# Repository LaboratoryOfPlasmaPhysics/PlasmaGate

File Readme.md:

# PlasmaGate: Open-Source FPGA Development Board for laboratory instrumentation

PlasmaGate is an open-source FPGA development board designed for laboratory instrumentation. It is based on the Lattice LFE5U-85F FPGA and designed to be used together with custom daughter boards. The board is equipped with a variety of interfaces including USB 2.0 HS, microSD, on board JTAG (rp2040), 44 GPIO pins, 32MB of SDRAM.

## Features
- Lattice LFE5U-85F FPGA
- USB 2.0 HS interface
- microSD card slot
- On-board JTAG interface using RP2040
- 44 GPIO pins
- 32MB SDRAM
- Customizable daughter board interface
- Open-source design

## Online view
You can view the board design online using kicanvas:
[PlasmaGate Board Design](https://kicanvas.org/?github=https%3A%2F%2Fgithub.com%2FLaboratoryOfPlasmaPhysics%2FPlasmaGate)

## Getting Started
TBD

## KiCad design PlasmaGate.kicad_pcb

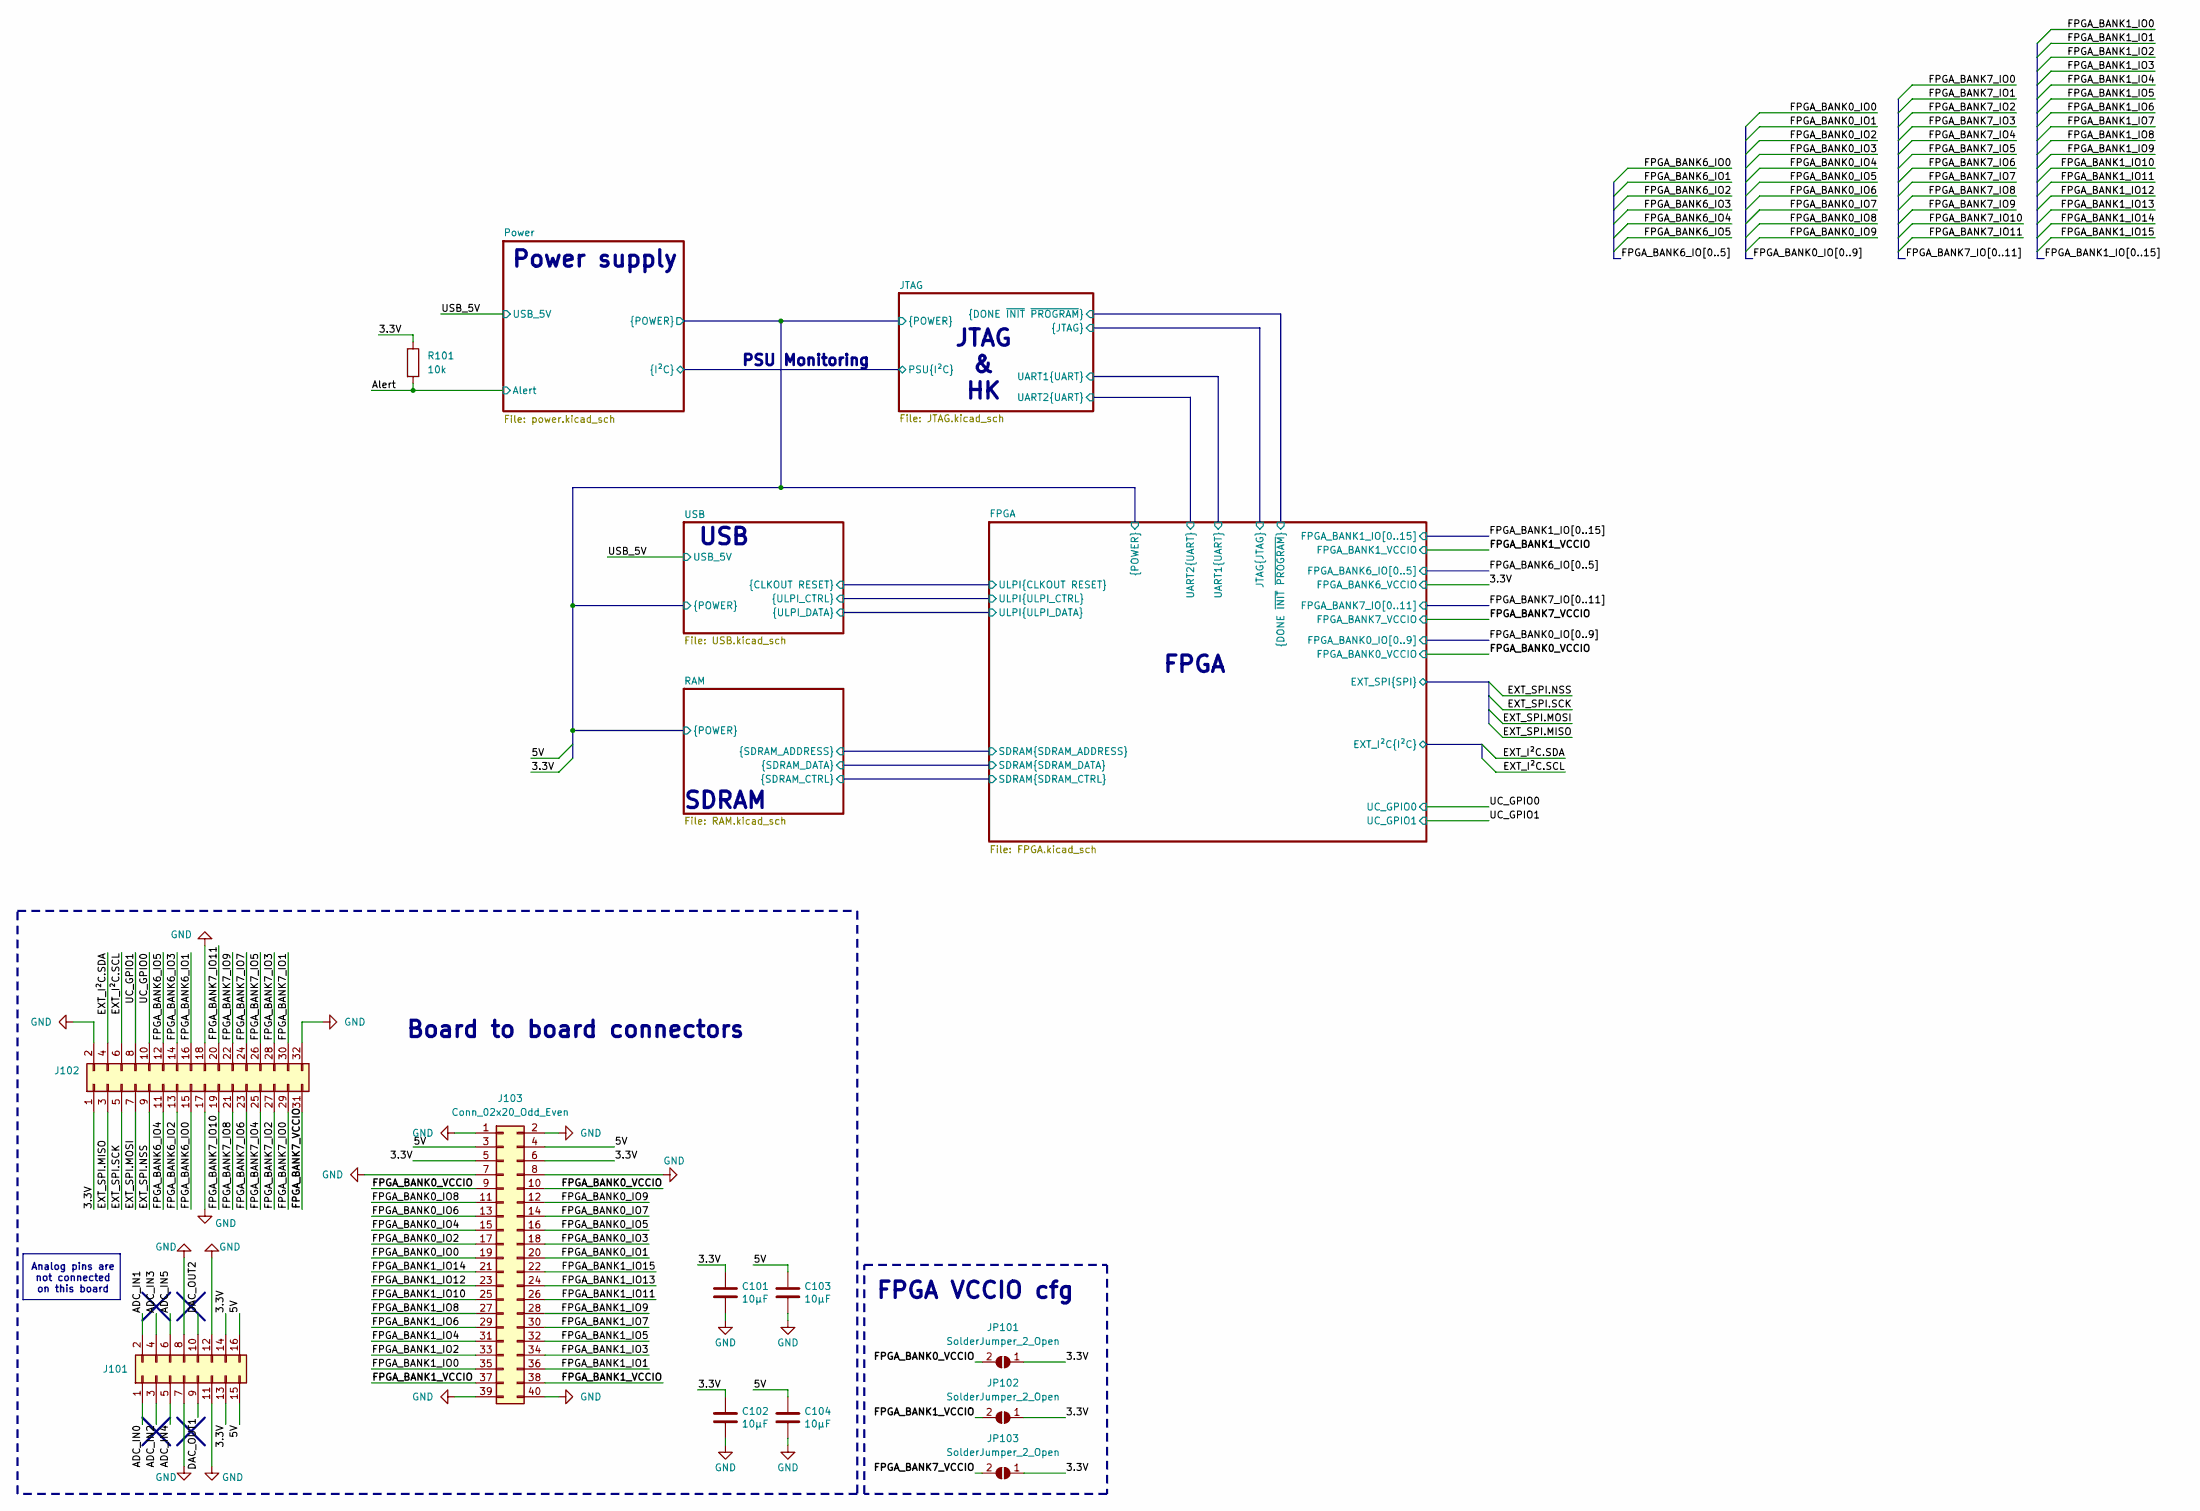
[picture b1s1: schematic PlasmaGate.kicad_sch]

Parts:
C101, C102, C103, C104: 10µF; C_1206_3216Metric_Pad1.33x1.80mm_HandSolder
J101: Conn_02x08_Odd_Even; PinSocket_2x08_P2.54mm_Vertical
J102: Conn_02x16_Odd_Even; PinSocket_2x16_P2.54mm_Vertical
J103: Conn_02x20_Odd_Even; PinSocket_2x20_P2.54mm_Vertical
JP101, JP102, JP103: SolderJumper_2_Open; SolderJumper-2_P1.3mm_Open_TrianglePad1.0x1.5mm
R101: 10k; R_0402_1005Metric_Pad0.72x0.64mm_HandSolder

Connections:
/ADC_IN0: J101.1
/ADC_IN1: J101.2
/ADC_IN2: J101.3
/ADC_IN3: J101.4
/ADC_IN4: J101.5
/ADC_IN5: J101.6
/Alert: R101.2; also elsewhere on the board
/DAC_OUT1: J101.9
/DAC_OUT2: J101.10
/FPGA/3.3V: C101.1, C102.1, J101.13, J101.14, J102.1, J103.5, J103.6, JP101.1 (A), JP102.1 (A), JP103.1 (A), R101.1; also elsewhere on the board
/FPGA/5V: C103.1, C104.1, J101.15, J101.16, J103.3, J103.4; also elsewhere on the board
/FPGA/EXT_I²C.SCL: J102.6; also elsewhere on the board
/FPGA/EXT_I²C.SDA: J102.4; also elsewhere on the board
/FPGA/EXT_SPI.MISO: J102.3; also elsewhere on the board
/FPGA/EXT_SPI.MOSI: J102.7; also elsewhere on the board
/FPGA/EXT_SPI.NSS: J102.9; also elsewhere on the board
/FPGA/EXT_SPI.SCK: J102.5; also elsewhere on the board
/FPGA_BANK0_IO0: J103.19; also elsewhere on the board
/FPGA_BANK0_IO1: J103.20; also elsewhere on the board
/FPGA_BANK0_IO2: J103.17; also elsewhere on the board
/FPGA_BANK0_IO3: J103.18; also elsewhere on the board
/FPGA_BANK0_IO4: J103.15; also elsewhere on the board
/FPGA_BANK0_IO5: J103.16; also elsewhere on the board
/FPGA_BANK0_IO6: J103.13; also elsewhere on the board
/FPGA_BANK0_IO7: J103.14; also elsewhere on the board
/FPGA_BANK0_IO8: J103.11; also elsewhere on the board
/FPGA_BANK0_IO9: J103.12; also elsewhere on the board
/FPGA_BANK0_VCCIO: J103.9, J103.10, JP101.2 (B); also elsewhere on the board
/FPGA_BANK1_IO0: J103.35; also elsewhere on the board
/FPGA_BANK1_IO1: J103.36; also elsewhere on the board
/FPGA_BANK1_IO2: J103.33; also elsewhere on the board
/FPGA_BANK1_IO3: J103.34; also elsewhere on the board
/FPGA_BANK1_IO4: J103.31; also elsewhere on the board
/FPGA_BANK1_IO5: J103.32; also elsewhere on the board
/FPGA_BANK1_IO6: J103.29; also elsewhere on the board
/FPGA_BANK1_IO7: J103.30; also elsewhere on the board
/FPGA_BANK1_IO8: J103.27; also elsewhere on the board
/FPGA_BANK1_IO9: J103.28; also elsewhere on the board
/FPGA_BANK1_IO10: J103.25; also elsewhere on the board
/FPGA_BANK1_IO11: J103.26; also elsewhere on the board
/FPGA_BANK1_IO12: J103.23; also elsewhere on the board
/FPGA_BANK1_IO13: J103.24; also elsewhere on the board
/FPGA_BANK1_IO14: J103.21; also elsewhere on the board
/FPGA_BANK1_IO15: J103.22; also elsewhere on the board
/FPGA_BANK1_VCCIO: J103.37, J103.38, JP102.2 (B); also elsewhere on the board
/FPGA_BANK6_IO0: J102.15; also elsewhere on the board
/FPGA_BANK6_IO1: J102.16; also elsewhere on the board
/FPGA_BANK6_IO2: J102.13; also elsewhere on the board
/FPGA_BANK6_IO3: J102.14; also elsewhere on the board
/FPGA_BANK6_IO4: J102.11; also elsewhere on the board
/FPGA_BANK6_IO5: J102.12; also elsewhere on the board
/FPGA_BANK7_IO0: J102.29; also elsewhere on the board
/FPGA_BANK7_IO1: J102.30; also elsewhere on the board
/FPGA_BANK7_IO2: J102.27; also elsewhere on the board
/FPGA_BANK7_IO3: J102.28; also elsewhere on the board
/FPGA_BANK7_IO4: J102.25; also elsewhere on the board
/FPGA_BANK7_IO5: J102.26; also elsewhere on the board
/FPGA_BANK7_IO6: J102.23; also elsewhere on the board
/FPGA_BANK7_IO7: J102.24; also elsewhere on the board
/FPGA_BANK7_IO8: J102.21; also elsewhere on the board
/FPGA_BANK7_IO9: J102.22; also elsewhere on the board
/FPGA_BANK7_IO10: J102.19; also elsewhere on the board
/FPGA_BANK7_IO11: J102.20; also elsewhere on the board
/FPGA_BANK7_VCCIO: J102.31, JP103.2 (B); also elsewhere on the board
/UC_GPIO0: J102.10; also elsewhere on the board
/UC_GPIO1: J102.8; also elsewhere on the board
GND: C101.2, C102.2, C103.2, C104.2, J101.7, J101.8, J101.11, J101.12, J102.2, J102.17, J102.18, J102.32, J103.1, J103.2, J103.7, J103.8, J103.39, J103.40; also elsewhere on the board

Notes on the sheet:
SDRAM
Board to board connectors
FPGA VCCIO cfg
PSU Monitoring
FPGA
JTAG & HK
Power supply
Analog pins are not connected on this board
USB

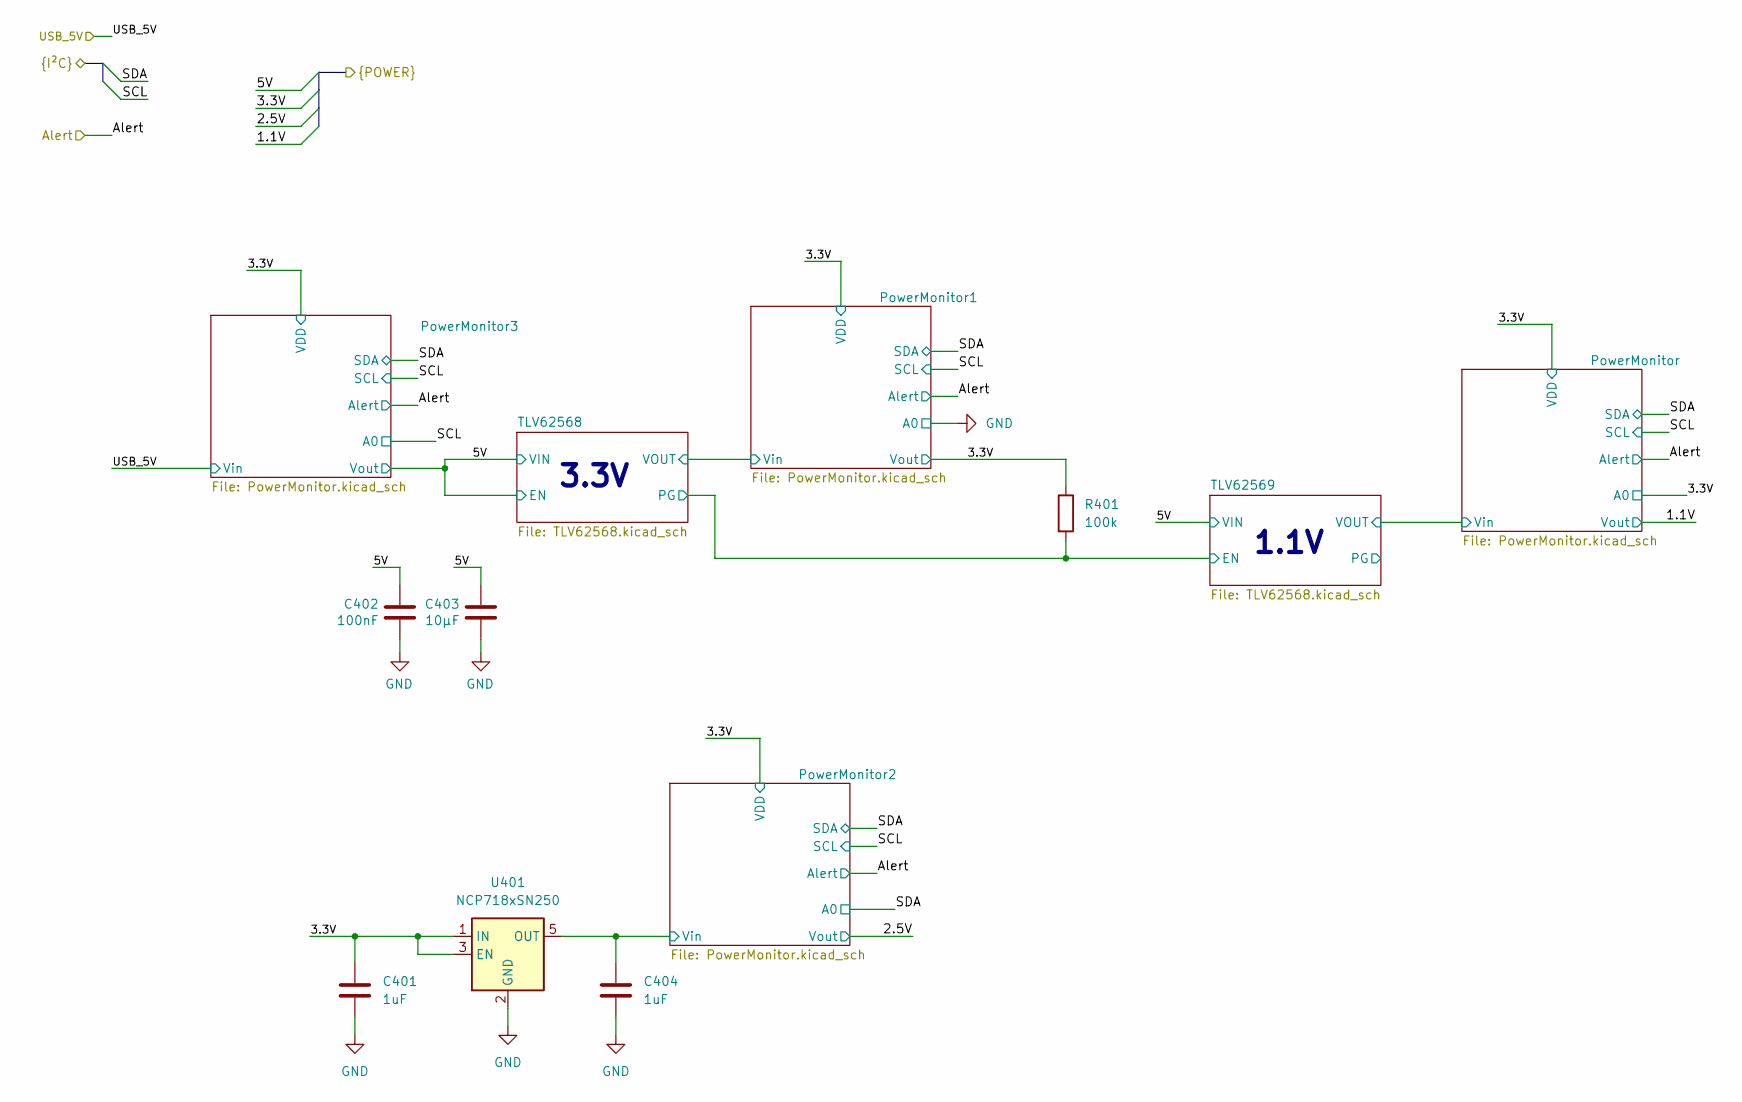
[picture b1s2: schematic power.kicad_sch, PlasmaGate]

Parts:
C401, C404: 1uF; C_0805_2012Metric_Pad1.18x1.45mm_HandSolder
C402: 100nF; C_0402_1005Metric_Pad0.74x0.62mm_HandSolder
C403: 10µF; C_1206_3216Metric_Pad1.33x1.80mm_HandSolder
R401: 100k; R_0402_1005Metric_Pad0.72x0.64mm_HandSolder
U401: NCP718xSN250; SOT-23-5

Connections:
/FPGA/3.3V: C401.1, R401.1, U401.1 (IN), U401.3 (EN); also elsewhere on the board
/FPGA/5V: C402.1, C403.1; also elsewhere on the board
/Power/PowerMonitor2/Vin: C404.1, U401.5 (OUT); also elsewhere on the board
/Power/TLV62568/PG: R401.2; also elsewhere on the board
GND: C401.2, C402.2, C403.2, C404.2, U401.2 (GND); also elsewhere on the board

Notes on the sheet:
1.1V
3.3V

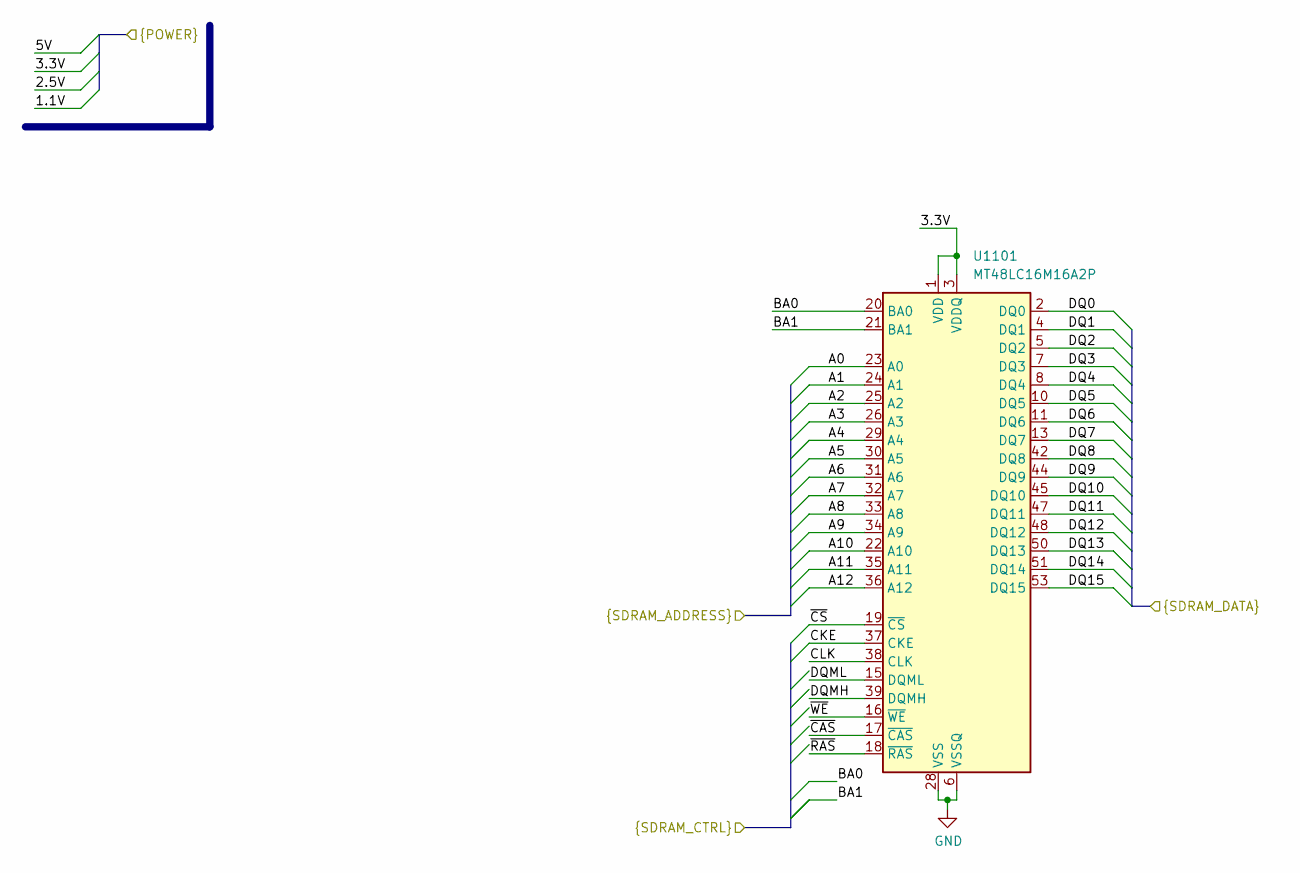
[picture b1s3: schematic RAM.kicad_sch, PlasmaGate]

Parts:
U1101: MT48LC16M16A2P; TSOP-II-54_22.2x10.16mm_P0.8mm

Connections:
/FPGA/3.3V: U1101.1 (VDD), U1101.3 (VDDQ), U1101.9 (VDDQ), U1101.14 (VDD), U1101.27 (VDD), U1101.43 (VDDQ), U1101.49 (VDDQ); also elsewhere on the board
/FPGA/SDRAM.A0: U1101.23 (A0); also elsewhere on the board
/FPGA/SDRAM.A1: U1101.24 (A1); also elsewhere on the board
/FPGA/SDRAM.A2: U1101.25 (A2); also elsewhere on the board
/FPGA/SDRAM.A3: U1101.26 (A3); also elsewhere on the board
/FPGA/SDRAM.A4: U1101.29 (A4); also elsewhere on the board
/FPGA/SDRAM.A5: U1101.30 (A5); also elsewhere on the board
/FPGA/SDRAM.A6: U1101.31 (A6); also elsewhere on the board
/FPGA/SDRAM.A7: U1101.32 (A7); also elsewhere on the board
/FPGA/SDRAM.A8: U1101.33 (A8); also elsewhere on the board
/FPGA/SDRAM.A9: U1101.34 (A9); also elsewhere on the board
/FPGA/SDRAM.A10: U1101.22 (A10); also elsewhere on the board
/FPGA/SDRAM.A11: U1101.35 (A11); also elsewhere on the board
/FPGA/SDRAM.A12: U1101.36 (A12); also elsewhere on the board
/FPGA/SDRAM.BA0: U1101.20 (BA0); also elsewhere on the board
/FPGA/SDRAM.BA1: U1101.21 (BA1); also elsewhere on the board
/FPGA/SDRAM.CKE: U1101.37 (CKE); also elsewhere on the board
/FPGA/SDRAM.CLK: U1101.38 (CLK); also elsewhere on the board
/FPGA/SDRAM.DQ0: U1101.2 (DQ0); also elsewhere on the board
/FPGA/SDRAM.DQ1: U1101.4 (DQ1); also elsewhere on the board
/FPGA/SDRAM.DQ2: U1101.5 (DQ2); also elsewhere on the board
/FPGA/SDRAM.DQ3: U1101.7 (DQ3); also elsewhere on the board
/FPGA/SDRAM.DQ4: U1101.8 (DQ4); also elsewhere on the board
/FPGA/SDRAM.DQ5: U1101.10 (DQ5); also elsewhere on the board
/FPGA/SDRAM.DQ6: U1101.11 (DQ6); also elsewhere on the board
/FPGA/SDRAM.DQ7: U1101.13 (DQ7); also elsewhere on the board
/FPGA/SDRAM.DQ8: U1101.42 (DQ8); also elsewhere on the board
/FPGA/SDRAM.DQ9: U1101.44 (DQ9); also elsewhere on the board
/FPGA/SDRAM.DQ10: U1101.45 (DQ10); also elsewhere on the board
/FPGA/SDRAM.DQ11: U1101.47 (DQ11); also elsewhere on the board
/FPGA/SDRAM.DQ12: U1101.48 (DQ12); also elsewhere on the board
/FPGA/SDRAM.DQ13: U1101.50 (DQ13); also elsewhere on the board
/FPGA/SDRAM.DQ14: U1101.51 (DQ14); also elsewhere on the board
/FPGA/SDRAM.DQ15: U1101.53 (DQ15); also elsewhere on the board
/FPGA/SDRAM.DQMH: U1101.39 (DQMH); also elsewhere on the board
/FPGA/SDRAM.DQML: U1101.15 (DQML); also elsewhere on the board
/FPGA/SDRAM.~CAS: U1101.17 (~CAS); also elsewhere on the board
/FPGA/SDRAM.~CS: U1101.19 (~CS); also elsewhere on the board
/FPGA/SDRAM.~RAS: U1101.18 (~RAS); also elsewhere on the board
/FPGA/SDRAM.~WE: U1101.16 (~WE); also elsewhere on the board
GND: U1101.6 (VSSQ), U1101.12 (VSSQ), U1101.28 (VSS), U1101.41 (VSS), U1101.46 (VSSQ), U1101.52 (VSSQ), U1101.54 (VSS); also elsewhere on the board

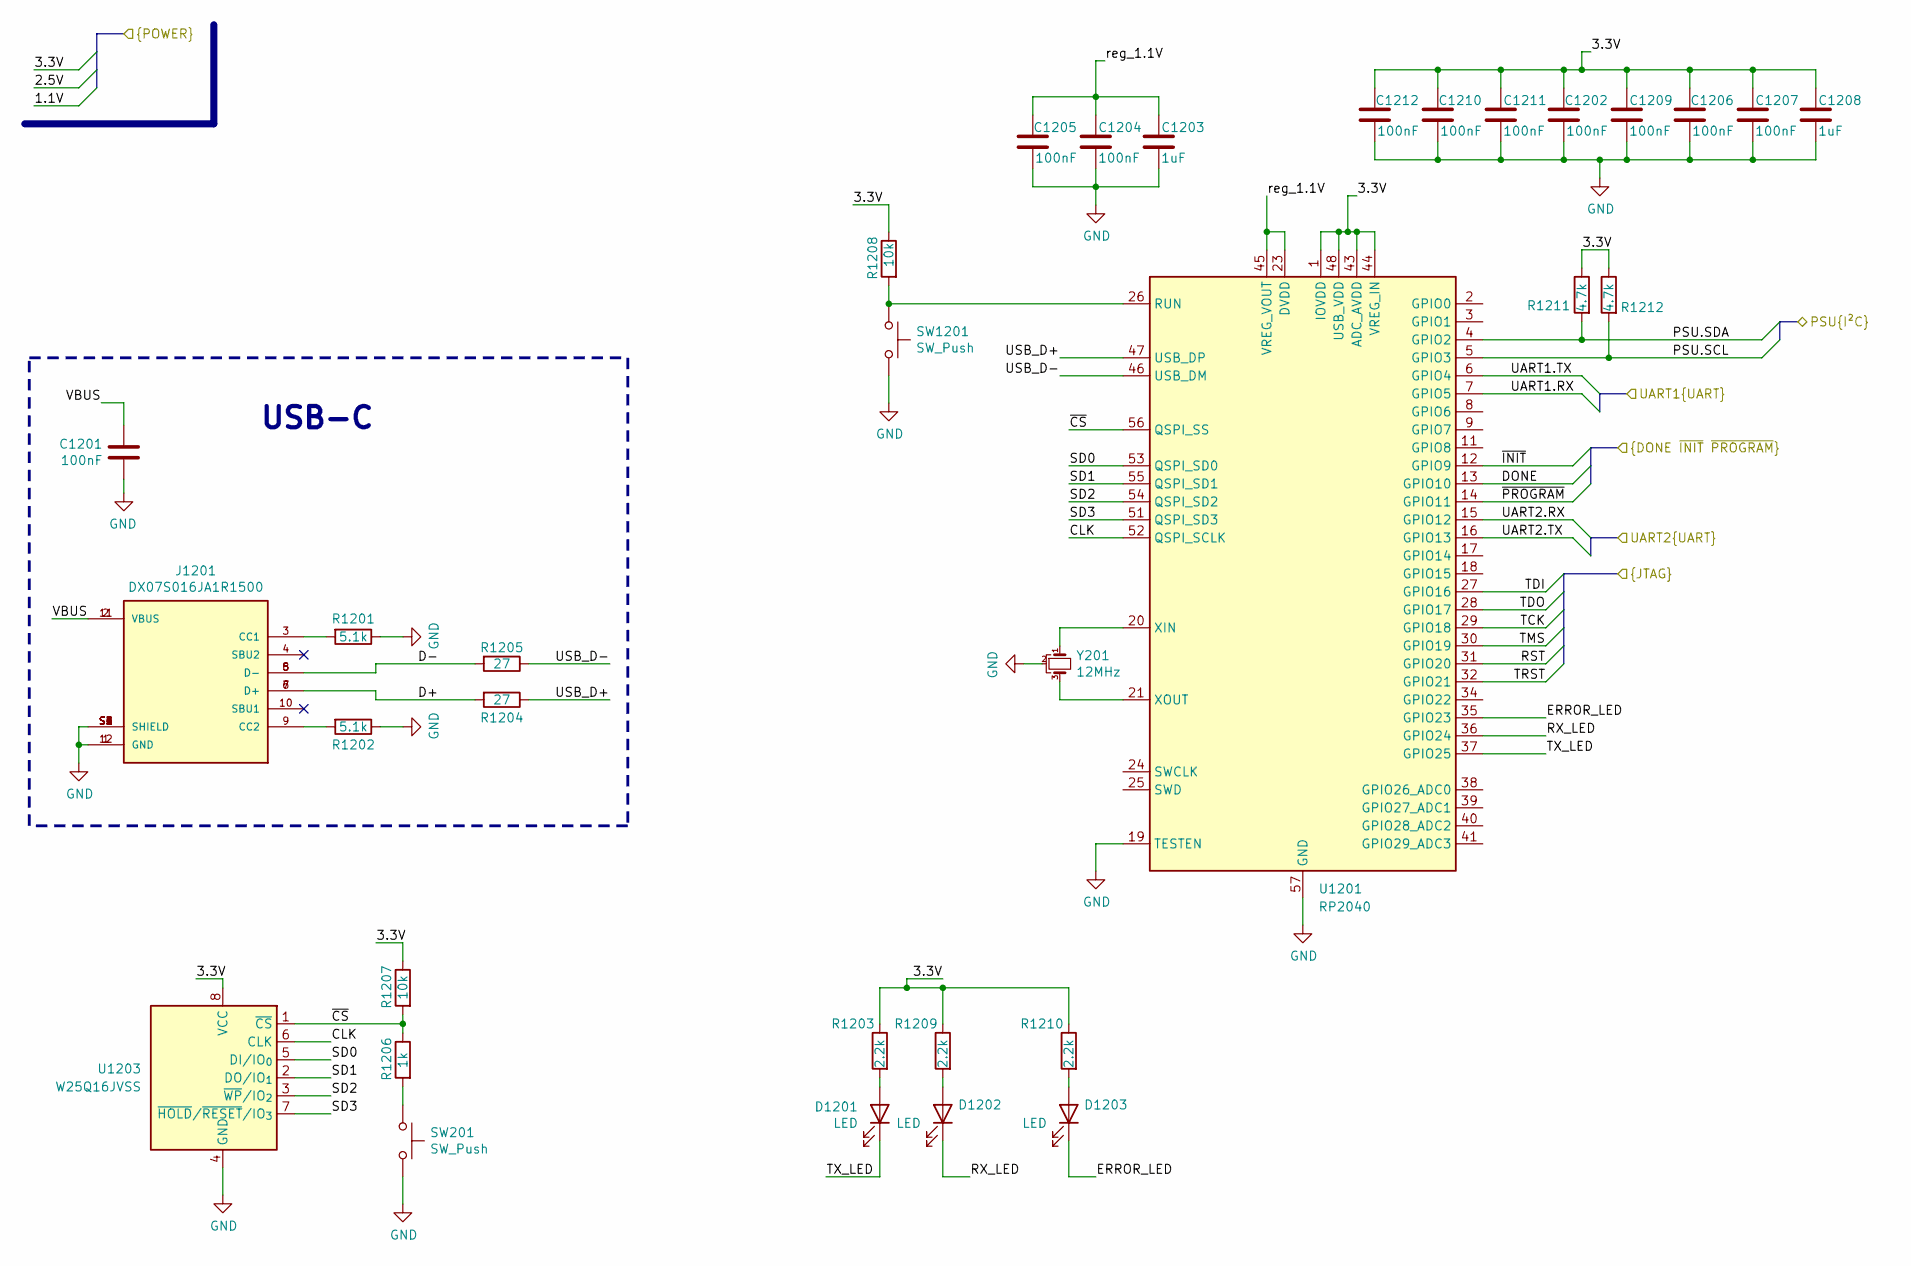
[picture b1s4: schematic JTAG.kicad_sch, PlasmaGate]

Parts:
C1201, C1202, C1206, C1207, C1209, C1210, C1211, C1212: 100nF; C_0402_1005Metric_Pad0.74x0.62mm_HandSolder
C1203, C1208: 1uF; C_0805_2012Metric_Pad1.18x1.45mm_HandSolder
C1204, C1205: 100nF; C_0603_1608Metric_Pad1.08x0.95mm_HandSolder
D1201, D1202, D1203: LED; LED_0603_1608Metric_Pad1.05x0.95mm_HandSolder
J1201: DX07S016JA1R1500; JAE_DX07S016JA1R1500; PARTREV 1
R1201, R1202: 5.1k; R_0402_1005Metric
R1203, R1209, R1210: 2.2k; R_0402_1005Metric_Pad0.72x0.64mm_HandSolder
R1204, R1205: 27; R_0402_1005Metric
R1206: 1k; R_0402_1005Metric
R1207: 10k; R_0402_1005Metric
R1208: 10k; R_0402_1005Metric_Pad0.72x0.64mm_HandSolder
R1211, R1212: 4.7k; R_0402_1005Metric_Pad0.72x0.64mm_HandSolder
SW201, SW1201: SW_Push; SW_SPST_TL3342
U1201: RP2040; QFN-56-1EP_7x7mm_P0.4mm_EP3.2x3.2mm
U1203: W25Q16JVSS; SOIC-8_5.3x5.3mm_P1.27mm
Y201: 12MHz; Resonator_SMD_Murata_CSTxExxV-3Pin_3.0x1.1mm_HandSoldering

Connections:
/FPGA/3.3V: C1202.1, C1206.1, C1207.1, C1208.1, C1209.1, C1210.1, C1211.1, C1212.1, R1203.1, R1207.1, R1208.1, R1209.1, R1210.1, R1211.1, R1212.1, U1201.1 (IOVDD), U1201.10 (IOVDD), U1201.22 (IOVDD), U1201.33 (IOVDD), U1201.42 (IOVDD), U1201.43 (ADC_AVDD), U1201.44 (VREG_IN), U1201.48 (USB_VDD), U1201.49 (IOVDD), U1203.8 (VCC); also elsewhere on the board
/FPGA/DONE: U1201.13 (GPIO10); also elsewhere on the board
/FPGA/JTAG.RST: U1201.31 (GPIO20)
/FPGA/JTAG.TCK: U1201.29 (GPIO18); also elsewhere on the board
/FPGA/JTAG.TDI: U1201.27 (GPIO16); also elsewhere on the board
/FPGA/JTAG.TDO: U1201.28 (GPIO17); also elsewhere on the board
/FPGA/JTAG.TMS: U1201.30 (GPIO19); also elsewhere on the board
/FPGA/JTAG.TRST: U1201.32 (GPIO21)
/FPGA/UART1.RX: U1201.7 (GPIO5); also elsewhere on the board
/FPGA/UART1.TX: U1201.6 (GPIO4); also elsewhere on the board
/FPGA/UART2.RX: U1201.15 (GPIO12); also elsewhere on the board
/FPGA/UART2.TX: U1201.16 (GPIO13); also elsewhere on the board
/FPGA/~INIT: U1201.12 (GPIO9); also elsewhere on the board
/FPGA/~PROGRAM: U1201.14 (GPIO11); also elsewhere on the board
/JTAG/CLK: U1201.52 (QSPI_SCLK), U1203.6 (CLK)
/JTAG/D+: J1201.6 (D+), J1201.7 (D+), R1204.2
/JTAG/D-: J1201.5 (D-), J1201.8 (D-), R1205.2
/JTAG/ERROR_LED: D1203.1 (K), U1201.35 (GPIO23)
/JTAG/PSU.SCL: R1212.2, U1201.5 (GPIO3); also elsewhere on the board
/JTAG/PSU.SDA: R1211.2, U1201.4 (GPIO2); also elsewhere on the board
/JTAG/RX_LED: D1202.1 (K), U1201.36 (GPIO24)
/JTAG/SD0: U1201.53 (QSPI_SD0), U1203.5 (DI/IO_{0})
/JTAG/SD1: U1201.55 (QSPI_SD1), U1203.2 (DO/IO_{1})
/JTAG/SD2: U1201.54 (QSPI_SD2), U1203.3 (~WP/IO_{2})
/JTAG/SD3: U1201.51 (QSPI_SD3), U1203.7 (~HOLD/~RESET/IO_{3})
/JTAG/TX_LED: D1201.1 (K), U1201.37 (GPIO25)
/JTAG/USB_D+: R1204.1, U1201.47 (USB_DP)
/JTAG/USB_D-: R1205.1, U1201.46 (USB_DM)
/JTAG/VBUS: C1201.1, J1201.2 (VBUS), J1201.11 (VBUS)
/JTAG/reg_1.1V: C1203.1, C1204.1, C1205.1, U1201.23 (DVDD), U1201.45 (VREG_VOUT), U1201.50 (DVDD)
/JTAG/~CS: R1206.1, R1207.2, U1201.56 (QSPI_SS), U1203.1 (~CS)
GND: C1201.2, C1202.2, C1203.2, C1204.2, C1205.2, C1206.2, C1207.2, C1208.2, C1209.2, C1210.2, C1211.2, C1212.2, J1201.1 (GND), J1201.12 (GND), J1201.S1 (SHIELD), J1201.S2 (SHIELD), J1201.S3 (SHIELD), J1201.S4 (SHIELD), J1201.S5 (SHIELD), J1201.S6 (SHIELD), R1201.1, R1202.1, SW201.2, SW1201.2, U1201.19 (TESTEN), U1201.57 (GND), U1203.4 (GND), Y201.2; also elsewhere on the board
unnamed: D1201.2 (A), R1203.2
unnamed: D1202.2 (A), R1209.2
unnamed: D1203.2 (A), R1210.2
unnamed: J1201.3 (CC1), R1201.2
unnamed: J1201.9 (CC2), R1202.2
unnamed: R1206.2, SW201.1
unnamed: R1208.2, SW1201.1, U1201.26 (RUN)
unnamed: U1201.20 (XIN), Y201.1
unnamed: U1201.21 (XOUT), Y201.3

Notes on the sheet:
USB-C

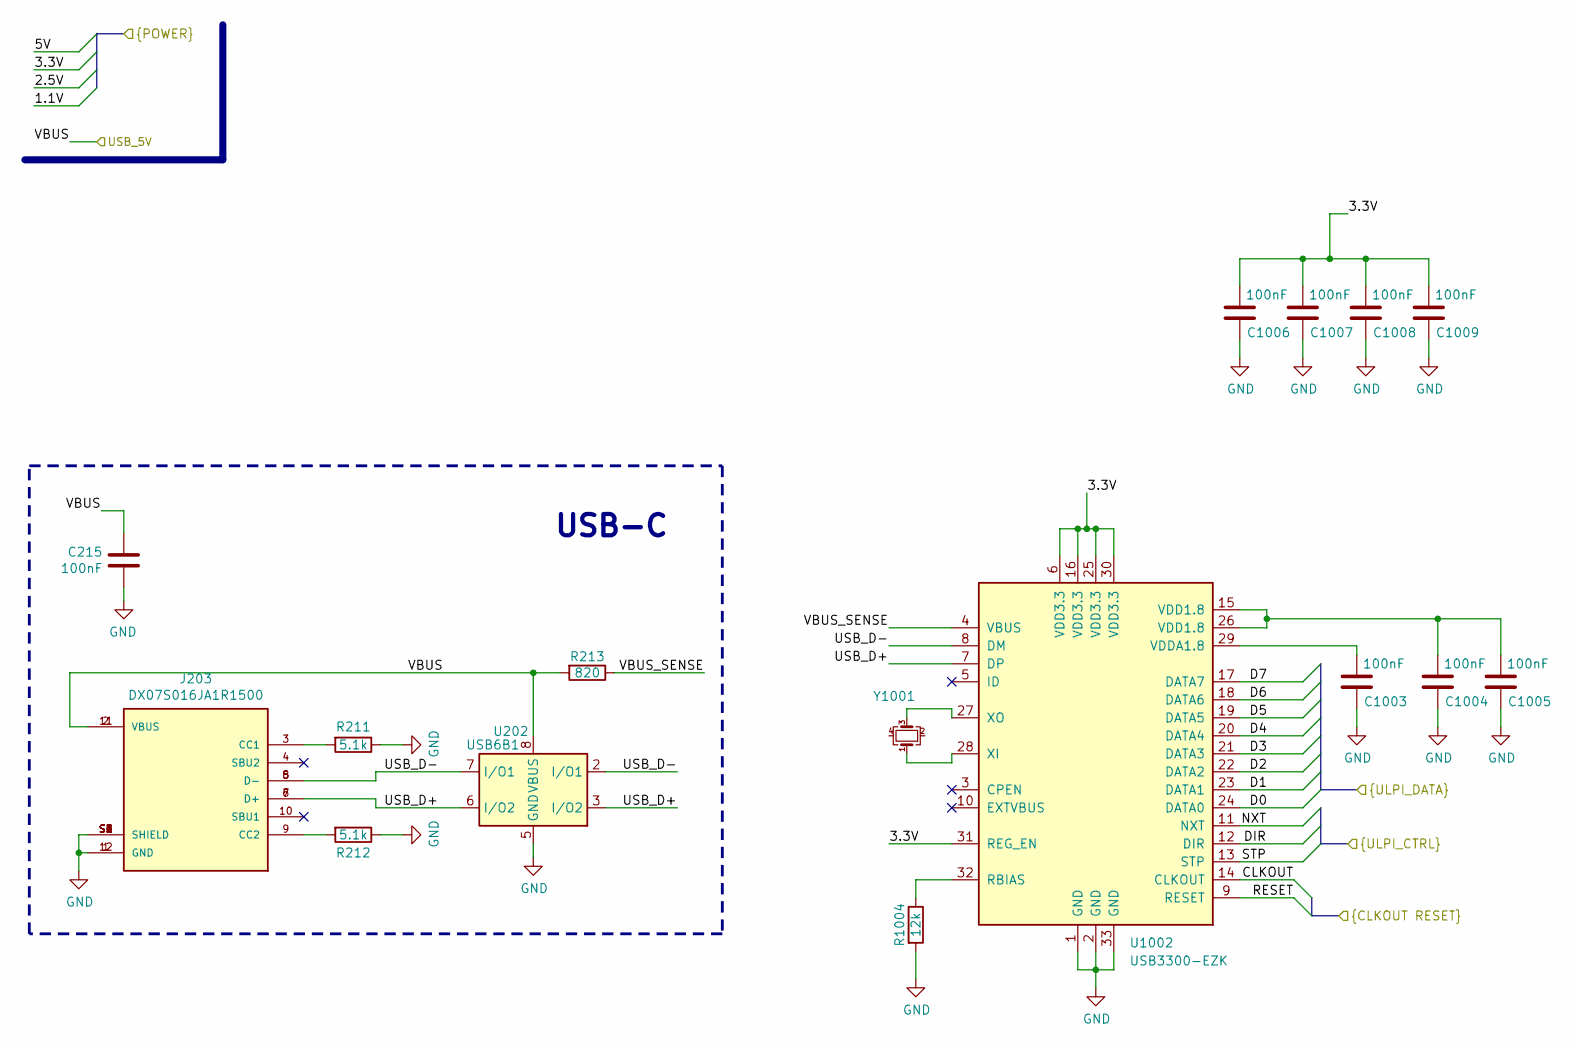
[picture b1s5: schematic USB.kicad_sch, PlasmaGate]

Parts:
C215, C1003, C1004, C1005, C1006, C1007, C1008, C1009: 100nF; C_0402_1005Metric_Pad0.74x0.62mm_HandSolder
J203: DX07S016JA1R1500; JAE_DX07S016JA1R1500; PARTREV 1
R211, R212: 5.1k; R_0402_1005Metric
R213: 820; R_0402_1005Metric
R1004: 12k; R_0402_1005Metric
U202: USB6B1; SOIC-8_3.9x4.9mm_P1.27mm
U1002: USB3300-EZK; QFN-32-1EP_5x5mm_P0.5mm_EP3.45x3.45mm
Y1001: Crystal_GND24_Small; Crystal_SMD_EuroQuartz_X22-4Pin_2.5x2.0mm_HandSoldering

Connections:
/FPGA/3.3V: C1006.1, C1007.1, C1008.1, C1009.1, U1002.6 (VDD3.3), U1002.16 (VDD3.3), U1002.25 (VDD3.3), U1002.30 (VDD3.3), U1002.31 (REG_EN); also elsewhere on the board
/FPGA/ULPI.CLKOUT: U1002.14 (CLKOUT); also elsewhere on the board
/FPGA/ULPI.D0: U1002.24 (DATA0); also elsewhere on the board
/FPGA/ULPI.D1: U1002.23 (DATA1); also elsewhere on the board
/FPGA/ULPI.D2: U1002.22 (DATA2); also elsewhere on the board
/FPGA/ULPI.D3: U1002.21 (DATA3); also elsewhere on the board
/FPGA/ULPI.D4: U1002.20 (DATA4); also elsewhere on the board
/FPGA/ULPI.D5: U1002.19 (DATA5); also elsewhere on the board
/FPGA/ULPI.D6: U1002.18 (DATA6); also elsewhere on the board
/FPGA/ULPI.D7: U1002.17 (DATA7); also elsewhere on the board
/FPGA/ULPI.DIR: U1002.12 (DIR); also elsewhere on the board
/FPGA/ULPI.NXT: U1002.11 (NXT); also elsewhere on the board
/FPGA/ULPI.RESET: U1002.9 (RESET); also elsewhere on the board
/FPGA/ULPI.STP: U1002.13 (STP); also elsewhere on the board
/USB/USB_D+: J203.6 (D+), J203.7 (D+), U202.3 (I/O2), U202.6 (I/O2), U1002.7 (DP)
/USB/USB_D-: J203.5 (D-), J203.8 (D-), U202.2 (I/O1), U202.7 (I/O1), U1002.8 (DM)
/USB/VBUS_SENSE: R213.1, U1002.4 (VBUS)
/USB_5V: C215.1, J203.2 (VBUS), J203.11 (VBUS), R213.2, U202.1 (VBUS), U202.8 (VBUS); also elsewhere on the board
GND: C215.2, C1003.2, C1004.2, C1005.2, C1006.2, C1007.2, C1008.2, C1009.2, J203.1 (GND), J203.12 (GND), J203.S1 (SHIELD), J203.S2 (SHIELD), J203.S3 (SHIELD), J203.S4 (SHIELD), J203.S5 (SHIELD), J203.S6 (SHIELD), R211.1, R212.1, R1004.2, U202.4 (GND), U202.5 (GND), U1002.1 (GND), U1002.2 (GND), U1002.33 (GND); also elsewhere on the board
unnamed: C1004.1, C1005.1, U1002.15 (VDD1.8), U1002.26 (VDD1.8)
unnamed: J203.3 (CC1), R211.2
unnamed: J203.9 (CC2), R212.2
unnamed: R1004.1, U1002.32 (RBIAS)
unnamed: C1003.1, U1002.29 (VDDA1.8)
unnamed: U1002.28 (XI), Y1001.1
unnamed: U1002.27 (XO), Y1001.3

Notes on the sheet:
USB-C

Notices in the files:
JTAG.kicad_sch:
CC-BY-SA
